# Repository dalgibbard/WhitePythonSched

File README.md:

# WhitePythonSched
Lighting controller code, to dim WhitePython LED's using a ULN2803A

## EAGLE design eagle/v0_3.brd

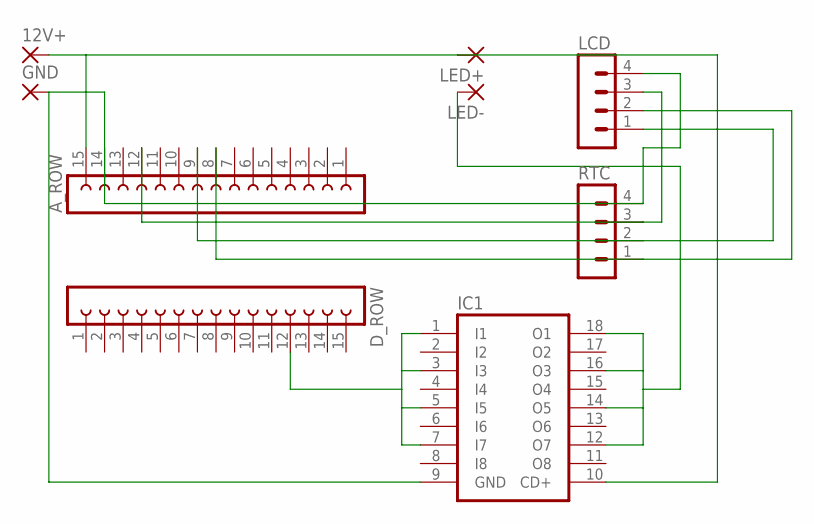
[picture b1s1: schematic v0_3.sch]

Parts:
12V+: 3,17/1,3
A_ROW: FE15-1; FE15
D_ROW: FE15-1; FE15
GND: 3,17/1,3
IC1: ULN2803A; DIL18
LCD: MA04-1
LED+: 3,17/1,3
LED-: 3,17/1,3
RTC: MA04-1

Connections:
unnamed: 12V+.1, A_ROW.15, IC1.10 (CD+), LED+.1
unnamed: A_ROW.14, GND.1, IC1.9 (GND), LCD.4, RTC.4
unnamed: IC1.12 (O7), IC1.14 (O5), IC1.16 (O3), IC1.18 (O1), LED-.1
unnamed: D_ROW.12, IC1.1 (I1), IC1.3 (I3), IC1.5 (I5), IC1.7 (I7)
unnamed: A_ROW.12, LCD.3, RTC.3
unnamed: A_ROW.8, LCD.2, RTC.1
unnamed: A_ROW.9, LCD.1, RTC.2

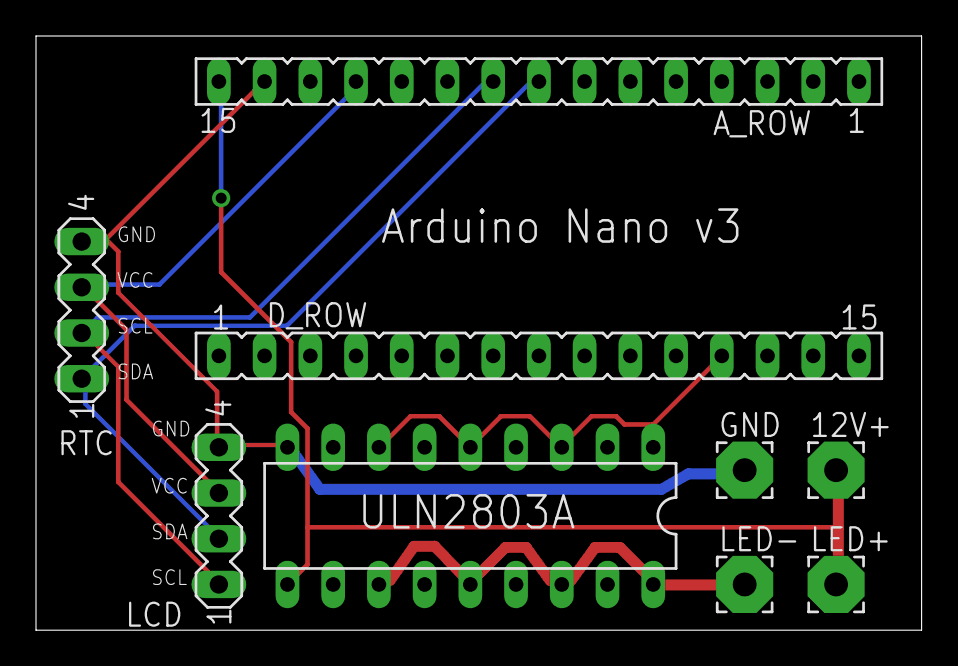
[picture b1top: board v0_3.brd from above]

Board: 2 copper layers, 49.2 x 33.0 mm, 9 parts (0 on the bottom side), 7 nets.

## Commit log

2015-02-15 Added Initial Code
2015-02-16 Added Final Product Image
2015-02-16 Renamed main file and added Eagle files
